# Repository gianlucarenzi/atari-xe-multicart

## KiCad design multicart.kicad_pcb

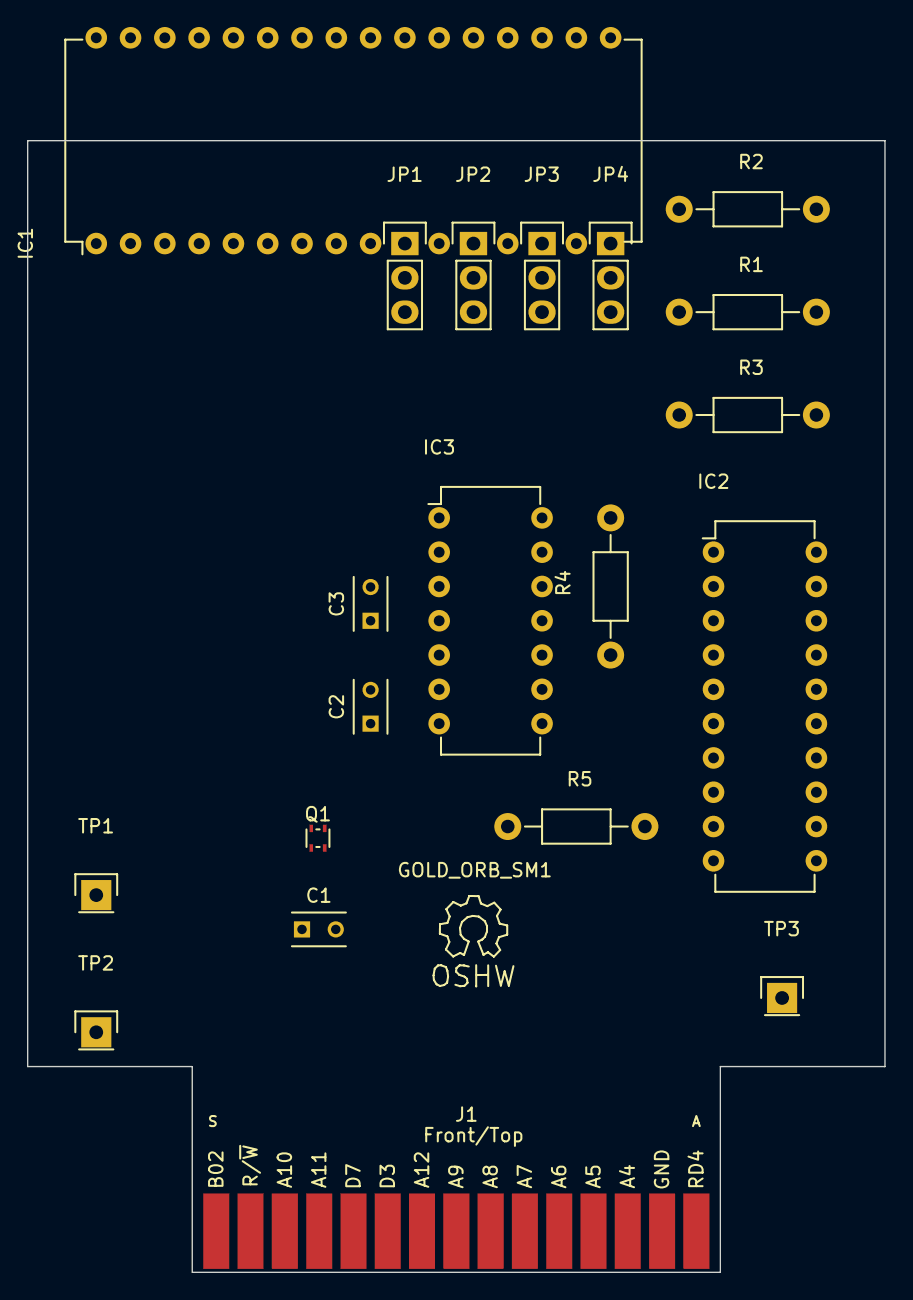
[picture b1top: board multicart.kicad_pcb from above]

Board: 2 copper layers, 63.5 x 83.8 mm, 21 parts (0 on the bottom side), 44 nets, no tracks yet.

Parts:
C1, C2, C3: 100n; C_Rect_L4_W2.5_P2.5
GOLD_ORB_SM1: OSHWLOGO_GOLD_ORB_SM; Symbol_OSHW-Logo_SilkScreen
IC1: 27C64-27C080; DIP-32_W15.24mm
IC2: 74373N; DIP-20_W7.62mm
IC3: 7408N; DIP-14_W7.62mm
J1: ATARI-800; ATARI-LEFT-CARTRIDGE
JP1, JP2, JP3, JP4: PINHD-1X3; Pin_Header_Straight_1x03
Q1: BS170; SOT-543
R1, R2, R3, R4, R5: 4k7; Resistor_Horizontal_RM10mm
TP1, TP2, TP3: TPB1,27; Pin_Header_Straight_1x01

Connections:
/A0: IC1.12, J1.5
/A1: IC1.11, J1.4
/A2: IC1.10, J1.3
/A3: IC1.9, J1.2
/A4: IC1.8, J1.C
/A5: IC1.7, J1.D
/A6: IC1.6, J1.E
/A7: IC1.5, J1.F
/A8: IC1.27, J1.H
/A9: IC1.26, J1.J
/A10: IC1.23, J1.P
/A11: IC1.25, J1.N
/A12: IC1.4, J1.K
/D0: IC1.13, J1.10
/D1: IC1.14, J1.9
/D2: IC1.15, J1.8
/D3: IC1.17, J1.L
/D4: IC1.18, J1.6
/D5: IC1.19, J1.7
/D6: IC1.20, J1.11
/D7: IC1.21, J1.M
GND: C1.2, C2.2, C3.2, IC1.16, IC1.22, IC2.1, IC2.10, IC3.7, J1.B
unnamed: IC1.1, JP1.2
unnamed: IC1.2, IC2.12
unnamed: IC1.3, IC2.15
unnamed: IC1.24, IC3.3
unnamed: IC1.28, IC3.6
unnamed: IC1.29, JP4.2
unnamed: IC1.30, JP3.2
unnamed: IC1.31, JP2.2
unnamed: IC2.2, J1.A
unnamed: IC2.5, JP1.3
unnamed: IC2.6, JP2.3
unnamed: IC2.9, JP3.3
unnamed: IC2.11, R4.2
unnamed: IC2.16, JP4.3
unnamed: IC2.19, IC3.5
unnamed: IC3.1, J1.12
unnamed: IC3.2, IC3.4, J1.1
unnamed: J1.14, R5.2
unnamed: JP1.1, R1.1
unnamed: JP2.1, R2.1
unnamed: JP4.1, R3.1
VCC: C1.1, C2.1, C3.1, IC1.32, IC2.20, IC3.14, J1.13, JP3.1, R1.2, R2.2, R3.2, R4.1, R5.1

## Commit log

2019-01-15 added. TO be clean
2025-11-06 deleted from repo
2025-11-06 New library name: RetroBitLab
